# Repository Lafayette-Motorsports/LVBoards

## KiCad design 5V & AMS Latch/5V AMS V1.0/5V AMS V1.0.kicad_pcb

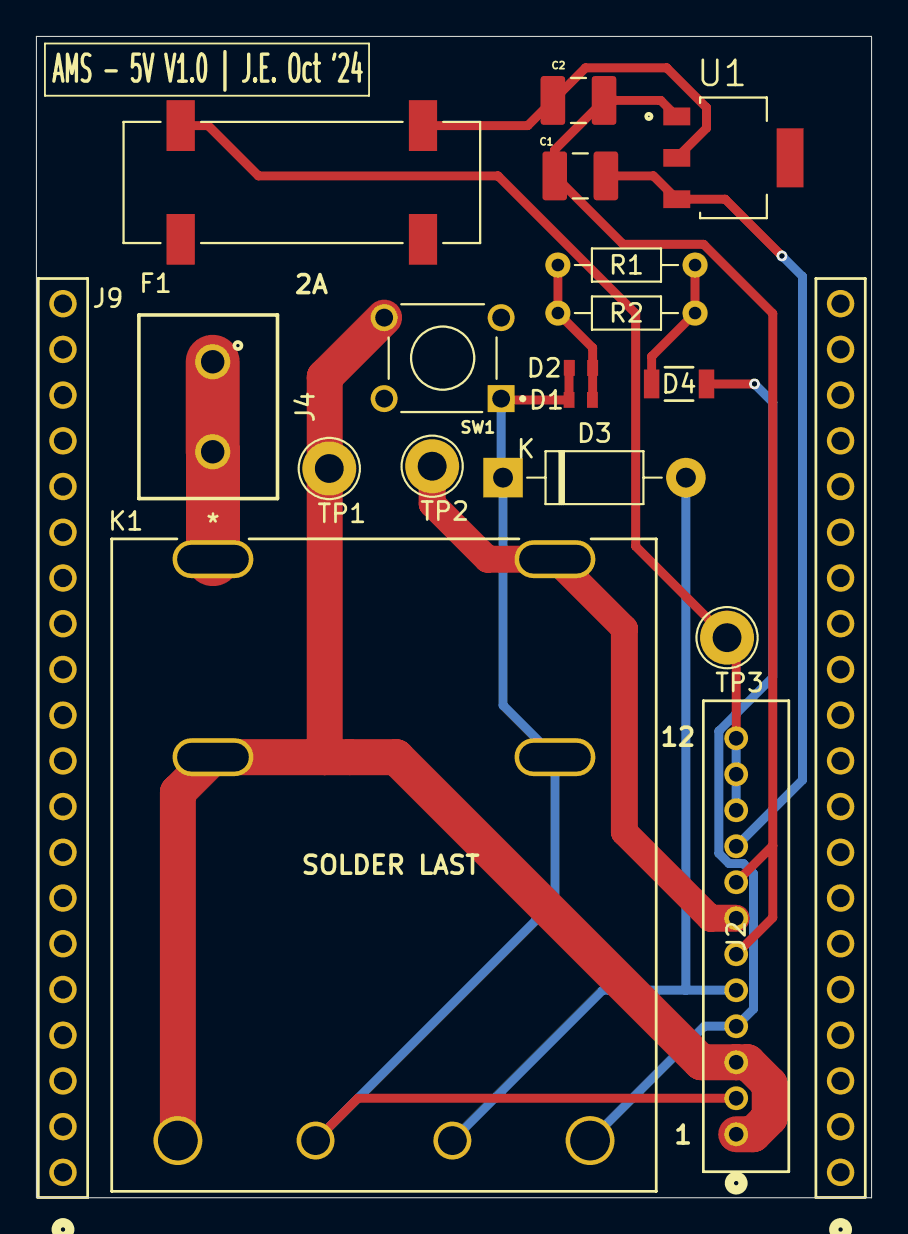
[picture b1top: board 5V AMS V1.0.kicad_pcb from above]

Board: 2 copper layers, 46.4 x 64.5 mm, 19 parts (0 on the bottom side), 11 nets.

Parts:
C1: 10u; CAPC3225X270N
C2: 47u; CAPC3225X270N
D1, D2: D_Zener; STA_RMCF0603_STP-L
D3: 1N4001; D_DO-41_SOD81_P10.16mm_Horizontal
D4: LED (Test); LED_AP3216SYD_KNB
F1: 3587TR; FUSE_3587
J2: B12B-PH-K-S; CONN12_B12B-PH_JST
J4: 691137710002
J6, J9: PH1-20-UA; CONN_PH1-20-UA_ADM
K1: AHES4291; AHES4_PAN
R1, R2: 1k; R_Axial_DIN0204_L3.6mm_D1.6mm_P7.62mm_Horizontal
SW1: Test Reset AMS; psuhButton
TP1, TP2, TP3: TestPoint; TestPoint_Loop_D2.60mm_Drill1.6mm_Beaded
U1: LT1117-5.0; REG_LT1117CST-5_TRPBF

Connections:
/GND: C1.2, C2.2, D1.2 (A), D2.2 (A), J2.6, J2.8, R1.1, R2.1, U1.1 (GND)
/Vs: C1.1, J2.9, U1.3 (VI)
unnamed: D1.1 (K), D2.1 (K), D3.1 (K), J2.2, K1.4, K1.7, SW1.1
unnamed: D3.2 (A), J2.5, K1.5
unnamed: D4.2 (A), J2.4, K1.6
unnamed: D4.1 (K), R1.2, R2.2
unnamed: F1.1_1, J2.10, J2.11, J2.12, TP3.1
unnamed: J2.1, J2.3, K1.2, K1.3, SW1.4, TP1.1
unnamed: J2.7, K1.8, TP2.1
unnamed: J4.1, J4.2, K1.1
unnamed: C2.1, F1.2_1, U1.2 (VO)

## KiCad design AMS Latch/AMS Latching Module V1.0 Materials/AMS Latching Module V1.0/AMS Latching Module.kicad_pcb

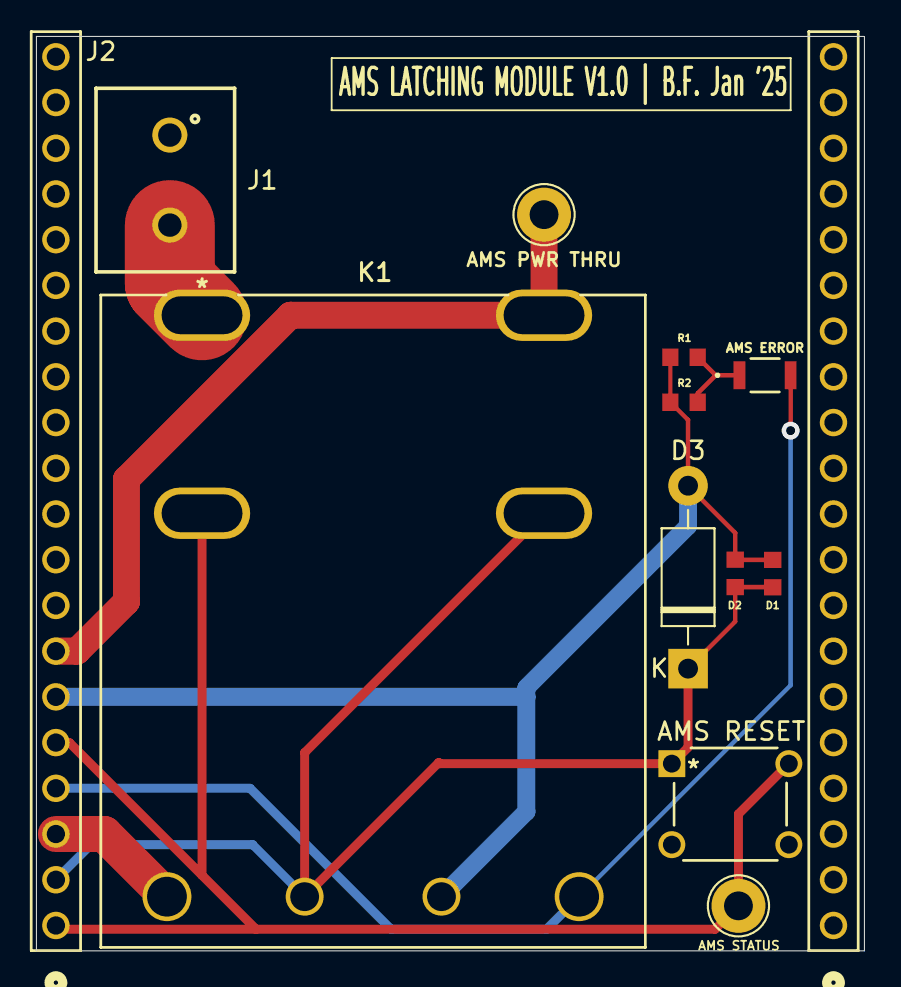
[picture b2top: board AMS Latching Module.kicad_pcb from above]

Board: 2 copper layers, 46.0 x 50.8 mm, 13 parts (0 on the bottom side), 8 nets.

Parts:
AMS: TestPoint; TestPoint_Loop_D2.60mm_Drill1.6mm_Beaded
AMS ERROR: LED (Test); LED_AP3216SYD_KNB-L
AMS PWR THRU: TestPoint; TestPoint_Loop_D2.60mm_Drill1.6mm_Beaded
AMS RESET: Test Reset AMS; SW4_1825910-B_TEC
D1, D2: D_Zener; RESC1508X55N
D3: 1N4001; D_DO-41_SOD81_P10.16mm_Horizontal
J1: 691137710002
J2, J2#2: PH1-20-UA; CONN_PH1-20-UA_ADM
K1: AHES4291; AHES4_PAN
R1, R2: 1k; RESC1508X55N

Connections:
/GND: D1.2 (A), D2.2 (A), D3.2 (A), J2.6, K1.5, R1.1, R2.1
/Vs: J2.3, K1.3
unnamed: AMS RESET.1, D1.1 (K), D2.1 (K), D3.1 (K), J2.2, K1.4, K1.7
unnamed: AMS ERROR.2 (A), J2.4, K1.6
unnamed: AMS ERROR.1 (K), R1.2, R2.2
unnamed: AMS.1, AMS RESET.2, J2.1, J2.5, K1.2
unnamed: AMS PWR THRU.1, J2.7, K1.8
unnamed: J1.2, K1.1

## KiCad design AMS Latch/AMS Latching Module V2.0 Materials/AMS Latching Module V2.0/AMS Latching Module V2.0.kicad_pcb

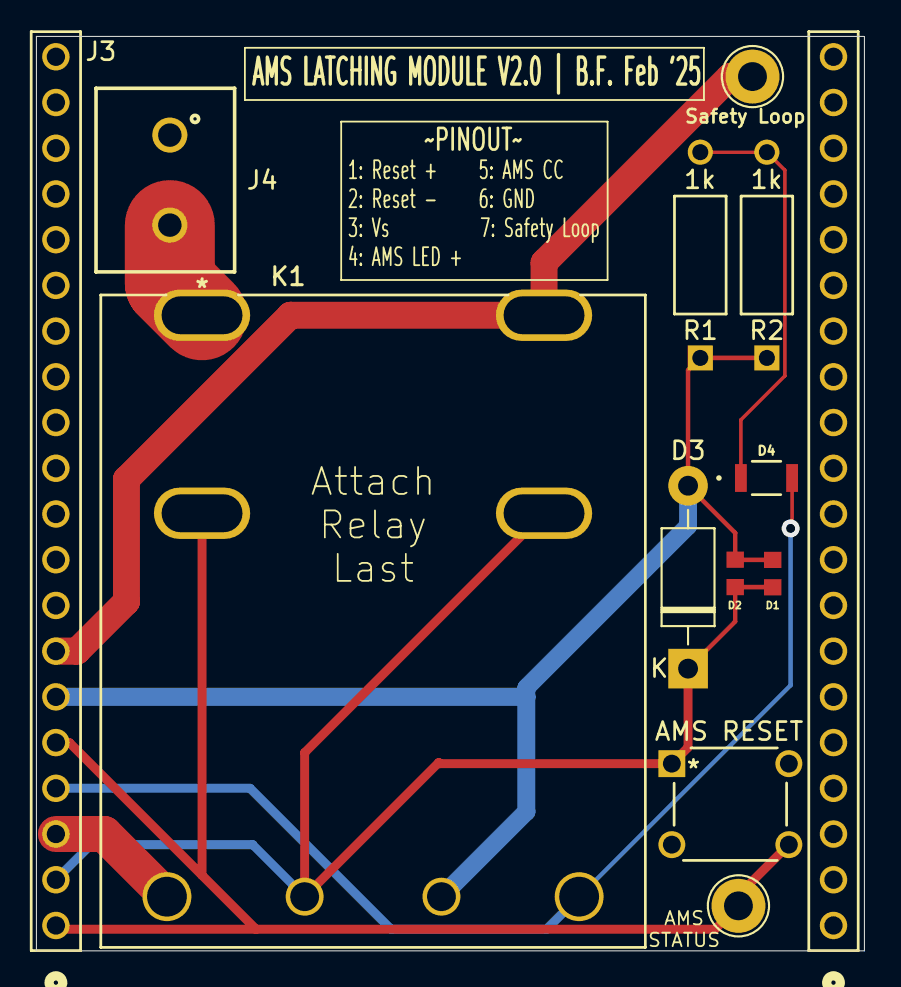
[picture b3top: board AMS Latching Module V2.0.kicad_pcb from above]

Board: 2 copper layers, 46.0 x 50.8 mm, 13 parts (0 on the bottom side), 8 nets.

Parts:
AMS RESET: Test Reset AMS; SW4_1825910-B_TEC
D1, D2: D_Zener; RESC1508X55N
D3: 1N4001; D_DO-41_SOD81_P10.16mm_Horizontal
D4: LED (Test); LED_AP3216SYD_KNB-L
J2, J3: PH1-20-UA; CONN_PH1-20-UA_ADM
J4: 691137710002
K1: AHES4291; AHES4_PAN
R1, R2: 1k; STA_CF14_STP
Safety Loop: TestPoint; TestPoint_Loop_D2.60mm_Drill1.6mm_Beaded
TP1: TestPoint; TestPoint_Loop_D2.60mm_Drill1.6mm_Beaded

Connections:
/GND: D1.2 (A), D2.2 (A), D3.2 (A), J3.6, K1.5, R1.1, R2.1
/Vs: J3.3, K1.3
unnamed: AMS RESET.1, D1.1 (K), D2.1 (K), D3.1 (K), J3.2, K1.4, K1.7
unnamed: D4.2 (A), J3.4, K1.6
unnamed: D4.1 (K), R1.2, R2.2
unnamed: AMS RESET.4, J3.1, J3.5, K1.2, TP1.1
unnamed: J3.7, K1.8, Safety Loop.1
unnamed: J4.2, K1.1

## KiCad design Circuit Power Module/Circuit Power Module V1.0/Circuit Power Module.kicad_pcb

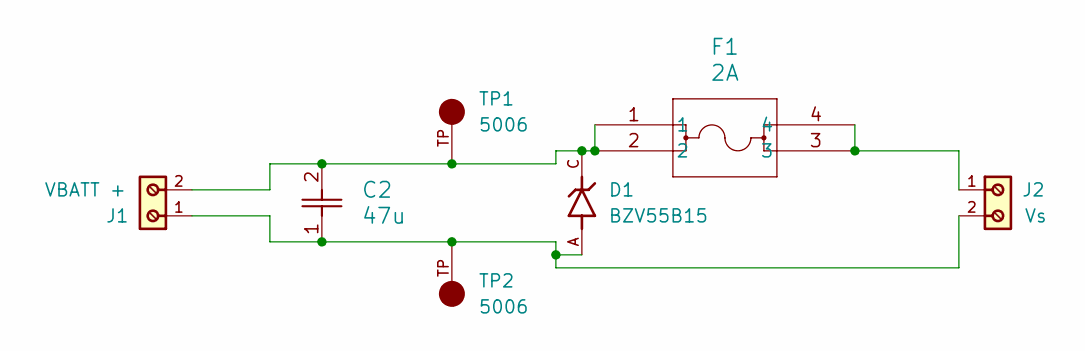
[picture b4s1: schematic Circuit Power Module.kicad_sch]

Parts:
C2: 47u; CAP_CL32_SAM-M
D1: BZV55B15; DIOMELF3515N; PARTREV F1804
F1: 2A; 3568_KEY
J1: VBATT +; 691137710002; PART-NUMBER 691137710002
J2: Vs; 691137710002; PART-NUMBER 691137710002
TP1, TP2: 5006; KEYSTONE_5006; PARTREV F

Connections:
unnamed: C2.1, D1.A, J1.1, J2.2, TP2.TP
unnamed: C2.2, D1.C, F1.1, F1.2, J1.2, TP1.TP
unnamed: F1.3, F1.4, J2.1

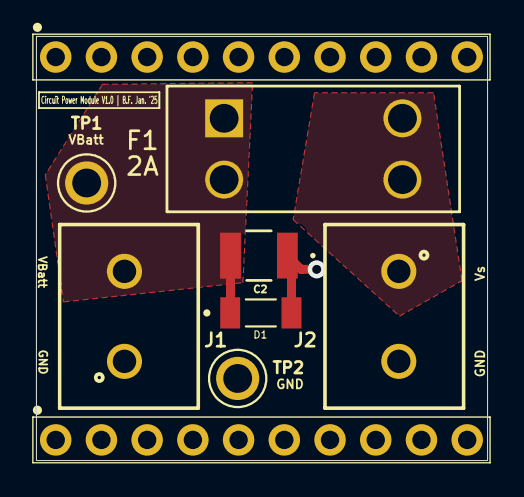
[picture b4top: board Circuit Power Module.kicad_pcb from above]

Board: 2 copper layers, 25.1 x 23.6 mm, 7 parts (0 on the bottom side), 3 nets.

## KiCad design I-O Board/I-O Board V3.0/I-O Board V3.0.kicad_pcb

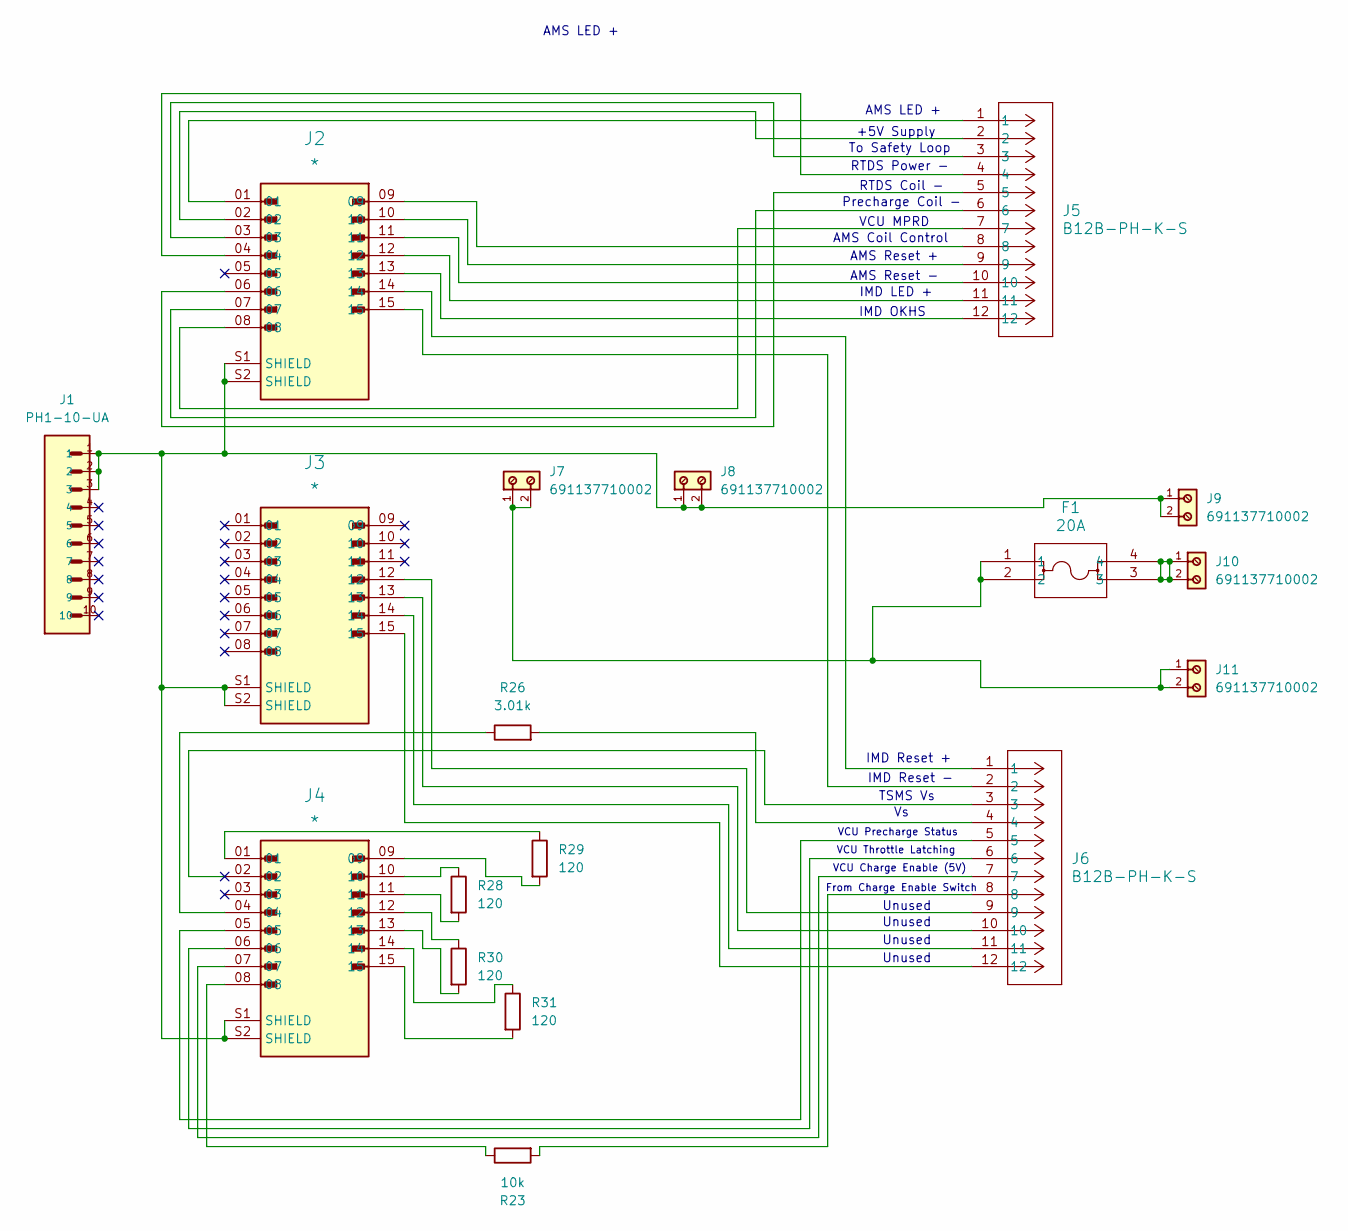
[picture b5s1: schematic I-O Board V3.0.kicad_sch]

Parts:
F1: 20A; 3568_KEY
J1: PH1-10-UA; HDRV10W64P0X254_1X10_2540X249X886P
J2, J3, J4: *; AMPHENOL_L717SDA15P1ACH4F
J5, J6: B12B-PH-K-S; CONN12_B12B-PH_JST
J7, J8, J9, J10, J11: 691137710002; PART-NUMBER 691137710002
R23: 10k; YAG_MF25_YAG
R26: 3.01k; YAG_MF25_YAG
R28, R29, R30, R31: 120; RESC3116X65N

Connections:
unnamed: F1.1, F1.2, J7.1, J7.2, J11.1, J11.2
unnamed: F1.3, F1.4, J10.1, J10.2
unnamed: J1.1, J1.2, J1.3, J2.S1 (SHIELD), J2.S2 (SHIELD), J3.S1 (SHIELD), J3.S2 (SHIELD), J4.S1 (SHIELD), J4.S2 (SHIELD), J8.1, J8.2, J9.1, J9.2
unnamed: J2.01, J5.1
unnamed: J2.02, J5.2
unnamed: J2.03, J5.3
unnamed: J2.04, J5.4
unnamed: J2.06, J5.5
unnamed: J2.07, J5.6
unnamed: J2.08, J5.7
unnamed: J2.09, J5.8
unnamed: J2.10, J5.9
unnamed: J2.11, J5.10
unnamed: J2.12, J5.11
unnamed: J2.13, J5.12
unnamed: J2.14, J6.1
unnamed: J2.15, J6.2
unnamed: J3.12, J6.9
unnamed: J3.13, J6.10
unnamed: J3.14, J6.11
unnamed: J3.15, J6.12
unnamed: J4.01, R29.1
unnamed: J4.04, R26.1
unnamed: J4.05, J6.5
unnamed: J4.06, J6.6
unnamed: J4.07, J6.7
unnamed: J4.08, R23.1
unnamed: J4.09, R29.2
unnamed: J4.10, R28.1
unnamed: J4.11, R28.2
unnamed: J4.12, R30.1
unnamed: J4.13, R30.2
unnamed: J4.14, R31.1
unnamed: J4.15, R31.2
unnamed: J6.4, R26.2
unnamed: J6.8, R23.2

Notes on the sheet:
AMS LED +
+5V Supply
IMD Reset -
VCU MPRD
IMD OKHS
RTDS Coil -
VCU Charge Enable (5V)
TSMS Vs
Unused
Unused
To Safety Loop
AMS Coil Control
From Charge Enable Switch
AMS Reset +
IMD Reset +
Precharge Coil -
VCU Throttle Latching
VCU Precharge Status
AMS Reset -
RTDS Power -
IMD LED +

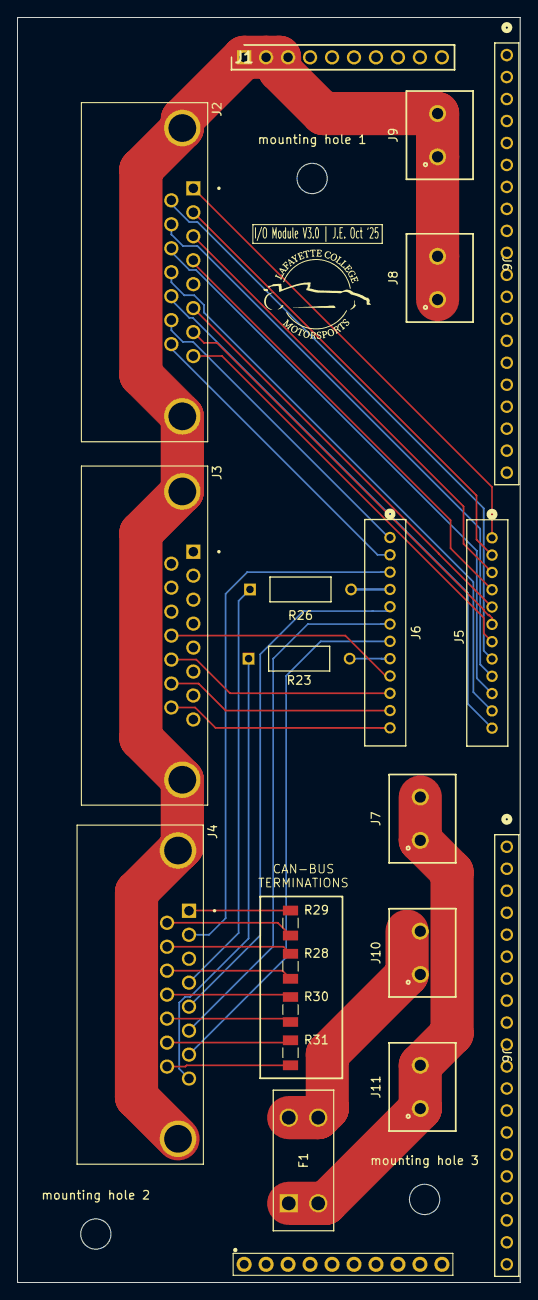
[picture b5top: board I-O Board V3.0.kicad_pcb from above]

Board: 2 copper layers, 58.1 x 146.2 mm, 23 parts (0 on the bottom side), 36 nets.

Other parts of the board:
J6#2, J6#3: 20-0600-21; CONN_20-0600-21_ARS
mounting hole 1, mounting hole 2, mounting hole 3: MountingHole_3.5mm
